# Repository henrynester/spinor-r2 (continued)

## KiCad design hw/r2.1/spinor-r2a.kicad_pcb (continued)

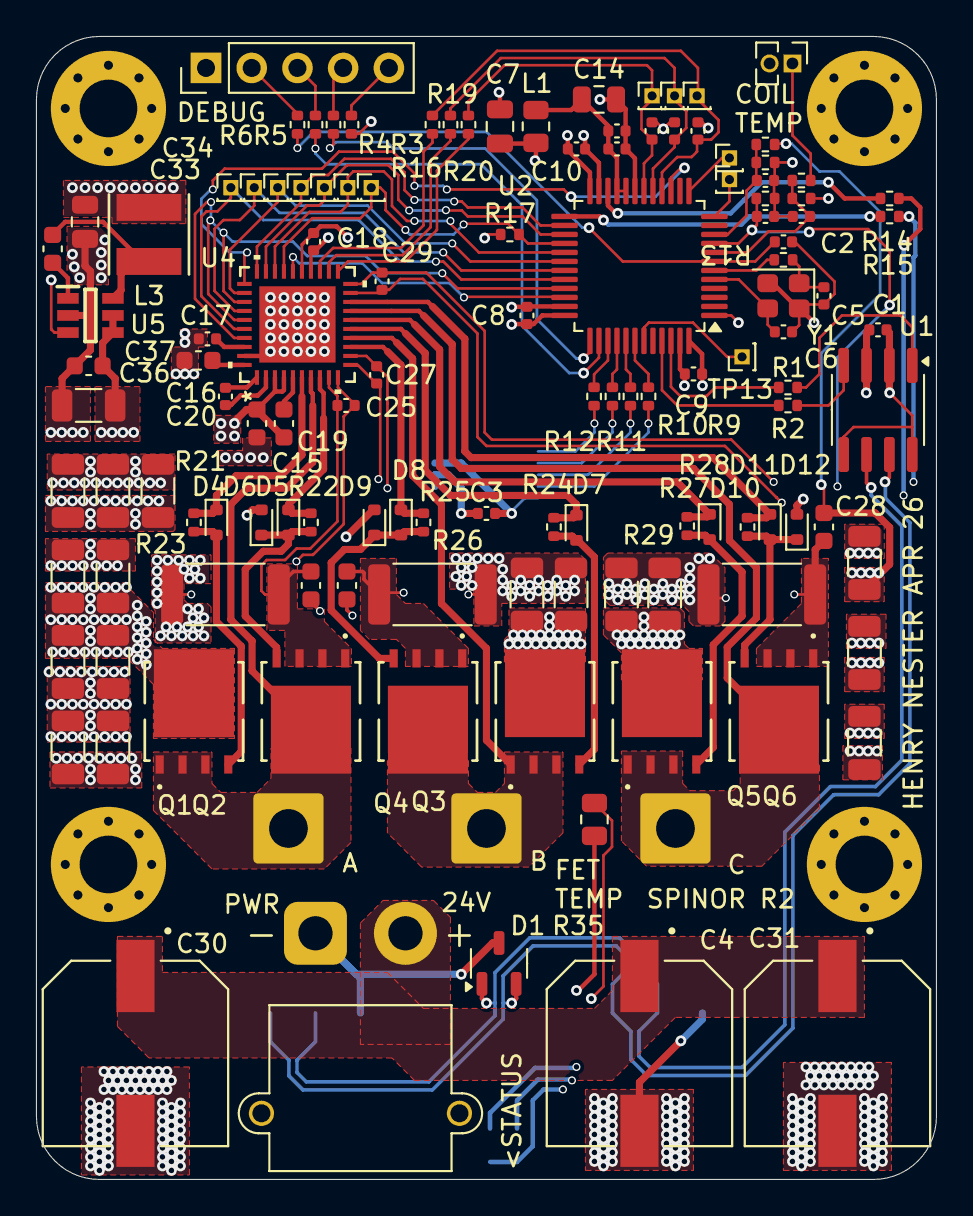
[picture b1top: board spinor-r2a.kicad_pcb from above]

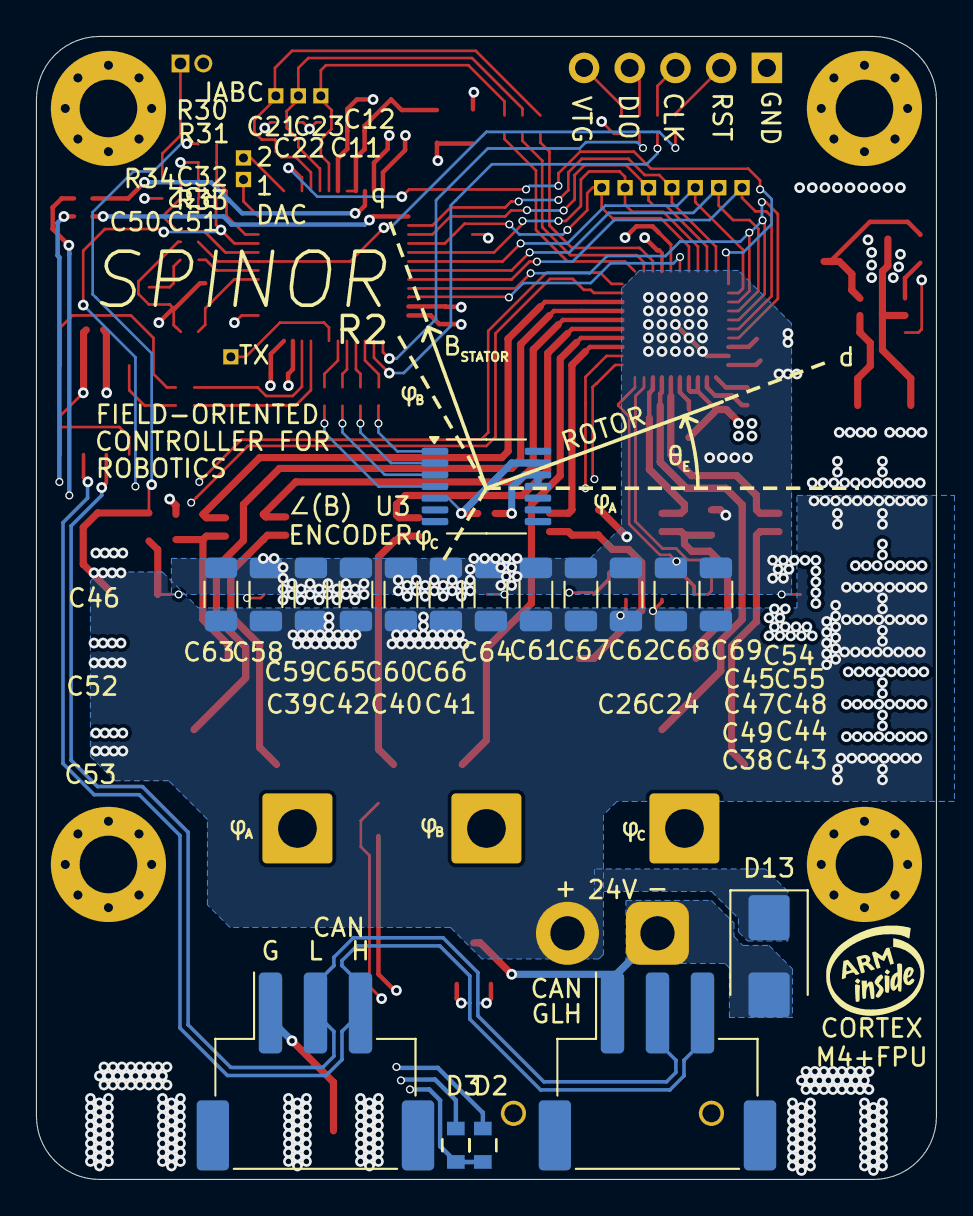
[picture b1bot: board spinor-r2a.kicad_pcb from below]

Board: 4 copper layers, 50.0 x 63.5 mm, 149 parts (18 on the bottom side), 80 nets.

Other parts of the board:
J9: Conn_01x05; PinHeader_1x05_P2.54mm_Vertical
TP13: PinHeader_1x01_P1.00mm_Vertical

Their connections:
/Microcontroller/DEBUG_NRST: J9.2; also elsewhere on the board
/Microcontroller/DEBUG_SWCLK: J9.3; also elsewhere on the board
/Microcontroller/DEBUG_SWDIO: J9.4; also elsewhere on the board
/Microcontroller/DEBUG_VTGT: J9.5; also elsewhere on the board
/Microcontroller/USART1_TX: TP13.1; also elsewhere on the board
GND: J9.1; also elsewhere on the board

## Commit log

2026-01-27 first upload
2026-01-30 start layout
2026-01-31 placed more components
2026-01-31 layout driver and 3v3 buck
2026-04-29 done routing!
2026-04-29 sent to R2.0 to jlcpcb
2026-05-01 make hw and fw folders
2026-06-20 archive c++ firmware
2026-06-20 create next board rev
